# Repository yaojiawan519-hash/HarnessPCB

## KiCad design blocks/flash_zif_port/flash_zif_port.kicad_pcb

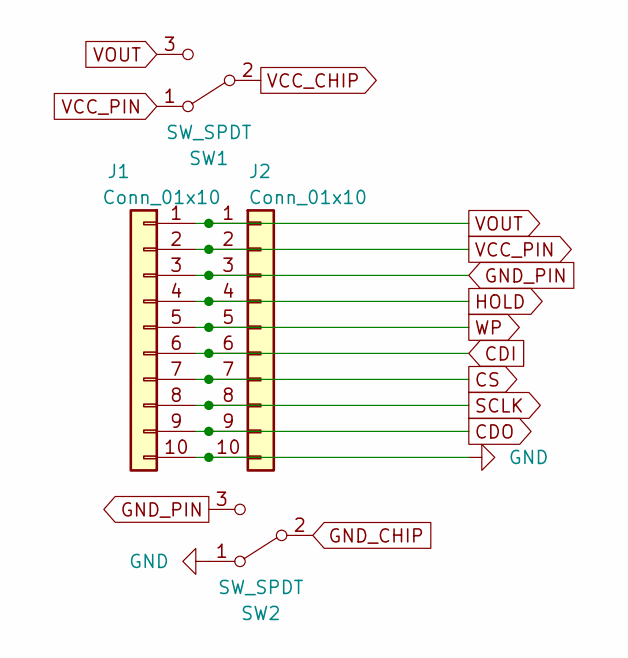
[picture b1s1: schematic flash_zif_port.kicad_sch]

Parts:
J1: Conn_01x10; PinSocket_1x10_P2.54mm_Horizontal
J2: Conn_01x10; PinHeader_1x10_P2.54mm_Vertical
SW1, SW2: SW_SPDT; SW_SPDT_PCM12

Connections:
CDI: J1.6, J2.6
CDO: J1.9, J2.9
CS: J1.7, J2.7
GND: J1.10, J2.10, SW2.1 (A)
GND_CHIP: SW2.2 (B)
GND_PIN: J1.3, J2.3, SW2.3 (C)
HOLD: J1.4, J2.4
SCLK: J1.8, J2.8
VCC_CHIP: SW1.2 (B)
VCC_PIN: J1.2, J2.2, SW1.1 (A)
VOUT: J1.1, J2.1, SW1.3 (C)
WP: J1.5, J2.5

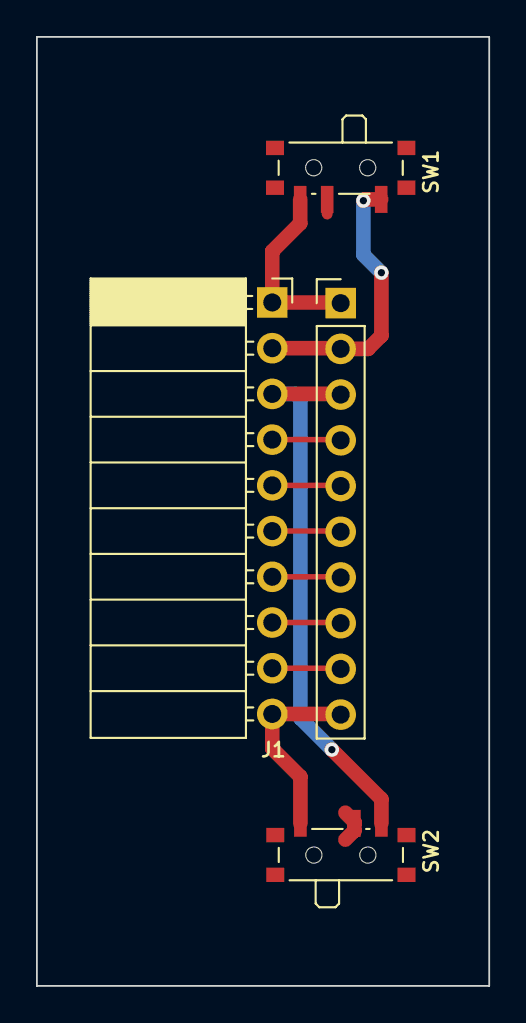
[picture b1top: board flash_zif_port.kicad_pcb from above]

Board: 2 copper layers, 25.1 x 52.7 mm, 4 parts (0 on the bottom side), 10 nets.

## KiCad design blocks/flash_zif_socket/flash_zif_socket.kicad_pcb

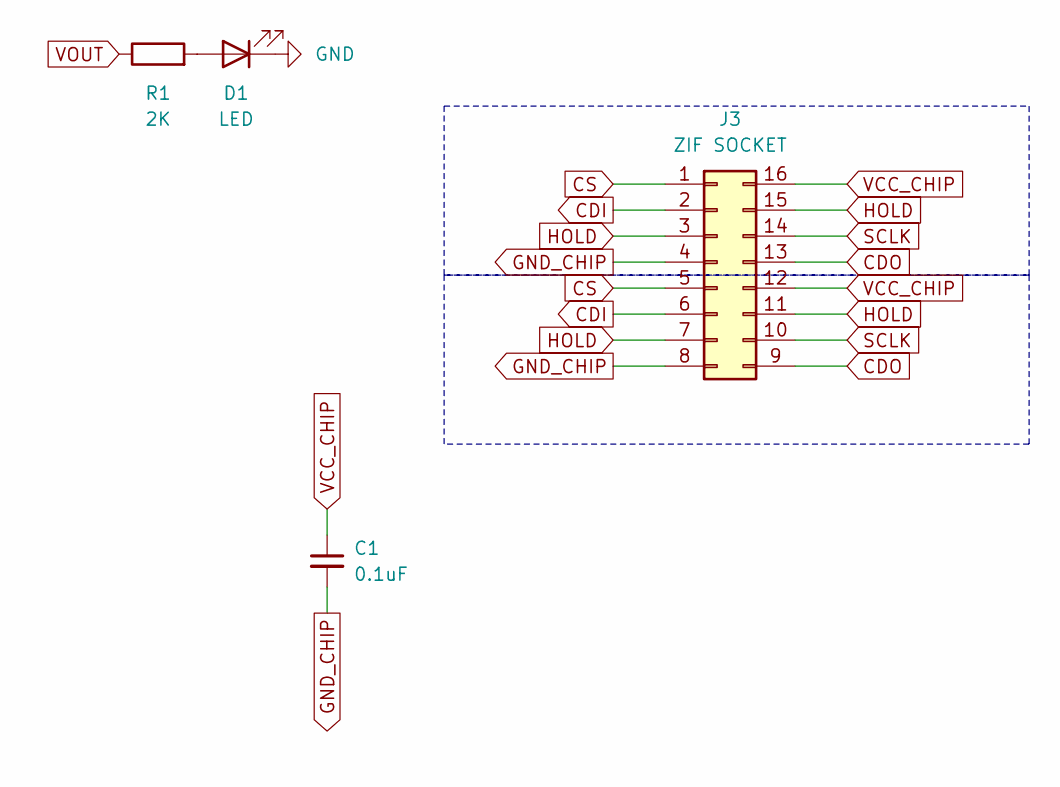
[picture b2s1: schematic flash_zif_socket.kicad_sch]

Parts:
C1: 0.1uF; C_0805_2012Metric
D1: LED; LED_0805_2012Metric
J3: ZIF SOCKET; DIP_Socket-16_W4.3_W5.08_W7.62_W10.16_W10.9_3M_216-3340-00-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
R1: 2K; R_0805_2012Metric

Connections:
CDI: J3.2, J3.6
CDO: J3.9, J3.13
CS: J3.1, J3.5
GND: D1.1 (K)
GND_CHIP: C1.2, J3.4, J3.8
HOLD: J3.3, J3.7, J3.11, J3.15
unnamed: D1.2 (A), R1.2
SCLK: J3.10, J3.14
VCC_CHIP: C1.1, J3.12, J3.16
VOUT: R1.1

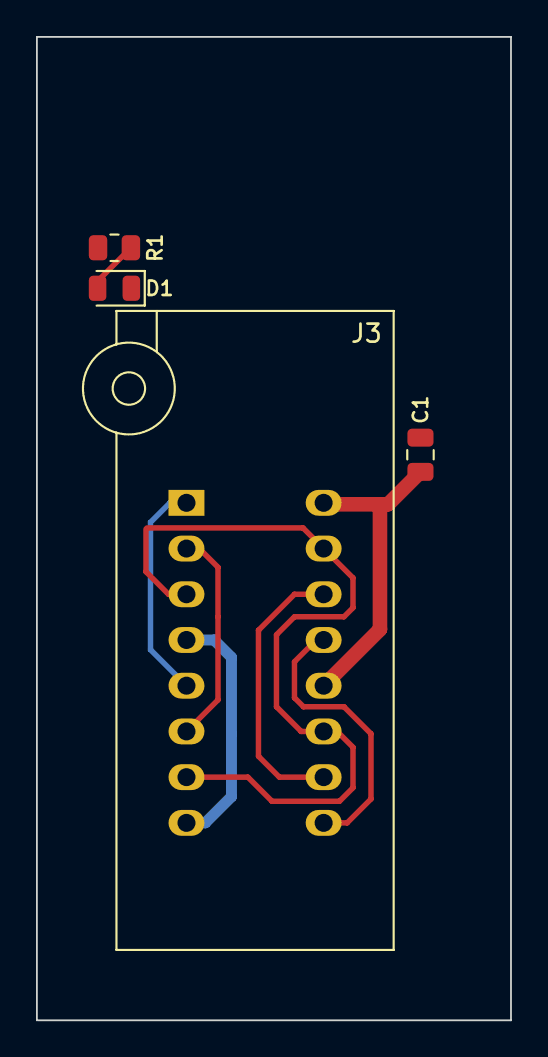
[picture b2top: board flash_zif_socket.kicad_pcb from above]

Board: 2 copper layers, 26.3 x 54.6 mm, 4 parts (0 on the bottom side), 8 nets.

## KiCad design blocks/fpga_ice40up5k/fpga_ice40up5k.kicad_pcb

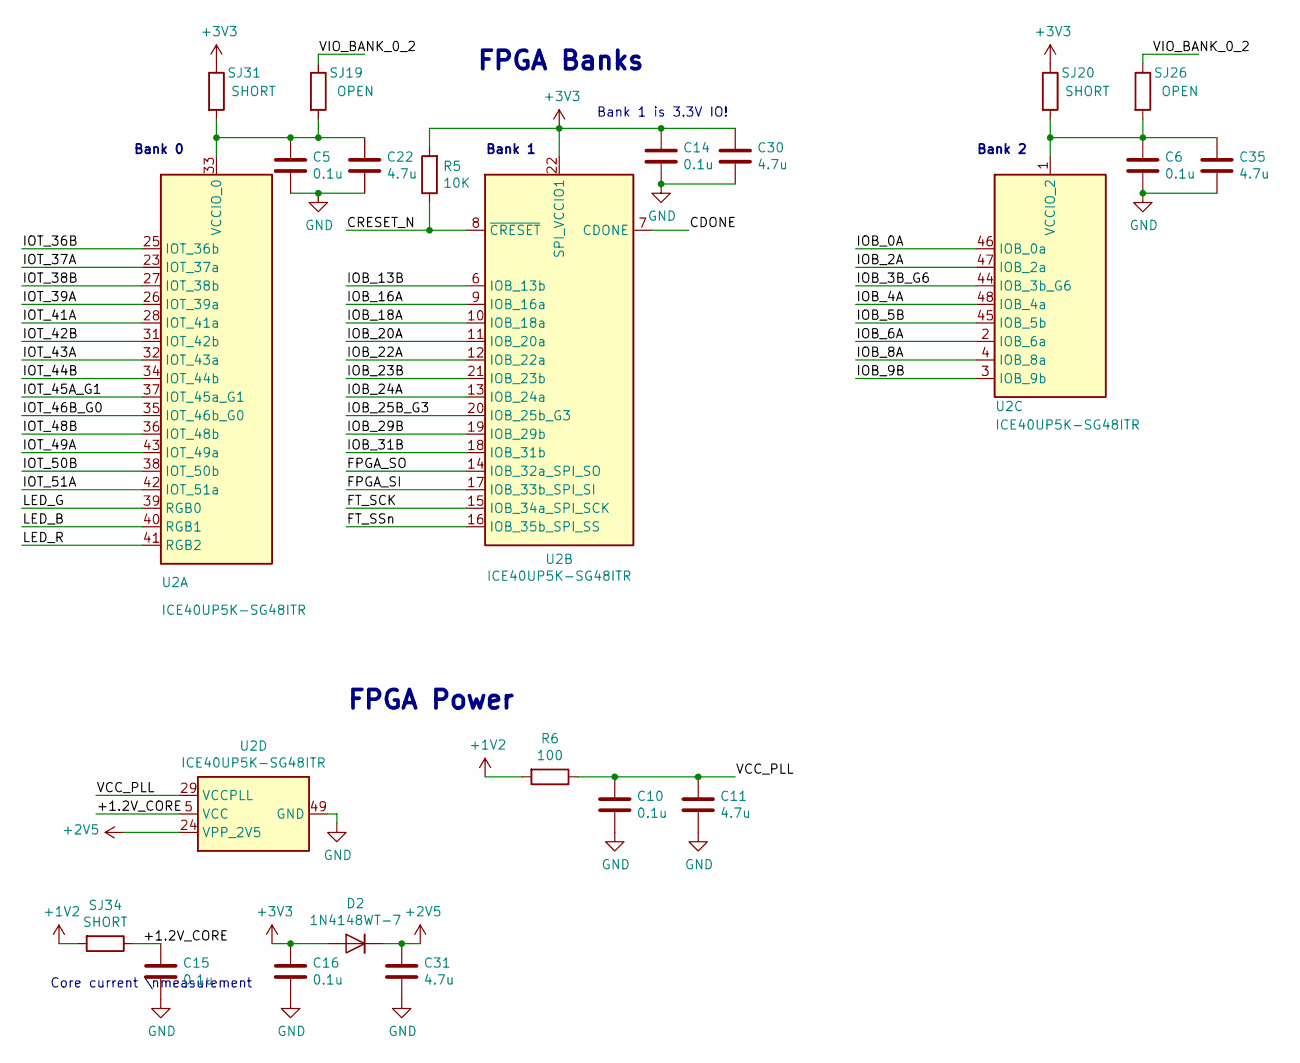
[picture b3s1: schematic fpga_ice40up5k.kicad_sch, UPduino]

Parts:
C5: 0.1u; C_0603_1608Metric; MPN C1005X5R0J104K050BA
C6, C10, C14, C15, C16: 0.1u; C_0603_1608Metric
C11, C22, C30, C31, C35: 4.7u; C_0603_1608Metric
D2: 1N4148WT-7; D_SOD-523
R5: 10K; R_0603_1608Metric
R6: 100; R_0603_1608Metric
SJ19, SJ26: OPEN; SolderJumper-2_0603_Open_TrianglePad1.0x1.5mm
SJ20, SJ31, SJ34: SHORT; ShortedJumper-2_P1.3mm_Bridged_Pad1.0x1.0mm
U2: ICE40UP5K-SG48ITR; QFN-48-1EP_7x7mm_P0.5mm_EP5.6x5.6mm

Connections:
+1V2: R6.2, SJ34.2
+2V5: C31.1, D2.1 (K), U2.24 (VPP_2V5)
+3V3: C14.1, C16.1, C30.1, D2.2 (A), R5.2, SJ20.1, SJ31.1, U2.22 (SPI_VCCIO1)
/+1.2V_CORE: C15.1, SJ34.1, U2.5 (VCC), U2.30 (VCC)
/CDONE: U2.7 (CDONE)
/CRESET_N: R5.1, U2.8 (~CRESET)
/FPGA_SI: U2.17 (IOB_33b_SPI_SI)
/FPGA_SO: U2.14 (IOB_32a_SPI_SO)
/FT_SCK: U2.15 (IOB_34a_SPI_SCK)
/FT_SSn: U2.16 (IOB_35b_SPI_SS)
/IOB_0A: U2.46 (IOB_0a)
/IOB_2A: U2.47 (IOB_2a)
/IOB_3B_G6: U2.44 (IOB_3b_G6)
/IOB_4A: U2.48 (IOB_4a)
/IOB_5B: U2.45 (IOB_5b)
/IOB_6A: U2.2 (IOB_6a)
/IOB_8A: U2.4 (IOB_8a)
/IOB_9B: U2.3 (IOB_9b)
/IOB_13B: U2.6 (IOB_13b)
/IOB_16A: U2.9 (IOB_16a)
/IOB_18A: U2.10 (IOB_18a)
/IOB_20A: U2.11 (IOB_20a)
/IOB_22A: U2.12 (IOB_22a)
/IOB_23B: U2.21 (IOB_23b)
/IOB_24A: U2.13 (IOB_24a)
/IOB_25B_G3: U2.20 (IOB_25b_G3)
/IOB_29B: U2.19 (IOB_29b)
/IOB_31B: U2.18 (IOB_31b)
/IOT_36B: U2.25 (IOT_36b)
/IOT_37A: U2.23 (IOT_37a)
/IOT_38B: U2.27 (IOT_38b)
/IOT_39A: U2.26 (IOT_39a)
/IOT_41A: U2.28 (IOT_41a)
/IOT_42B: U2.31 (IOT_42b)
/IOT_43A: U2.32 (IOT_43a)
/IOT_44B: U2.34 (IOT_44b)
/IOT_45A_G1: U2.37 (IOT_45a_G1)
/IOT_46B_G0: U2.35 (IOT_46b_G0)
/IOT_48B: U2.36 (IOT_48b)
/IOT_49A: U2.43 (IOT_49a)
/IOT_50B: U2.38 (IOT_50b)
/IOT_51A: U2.42 (IOT_51a)
/LED_B: U2.40 (RGB1)
/LED_G: U2.39 (RGB0)
/LED_R: U2.41 (RGB2)
/VCC_PLL: C10.1, C11.1, R6.1, U2.29 (VCCPLL)
/VIO_BANK_0_2: SJ19.1, SJ26.1
GND: C5.2, C6.2, C10.2, C11.2, C14.2, C15.2, C16.2, C22.2, C30.2, C31.2, C35.2, U2.49 (GND)
unnamed: C5.1, C22.1, SJ19.2, SJ31.2, U2.33 (VCCIO_0)
unnamed: C6.1, C35.1, SJ20.2, SJ26.2, U2.1 (VCCIO_2)

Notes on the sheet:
FPGA Banks
FPGA Power
Bank 2
Core current \nmeasurement
Bank 1
Bank 0
Bank 1 is 3.3V IO!

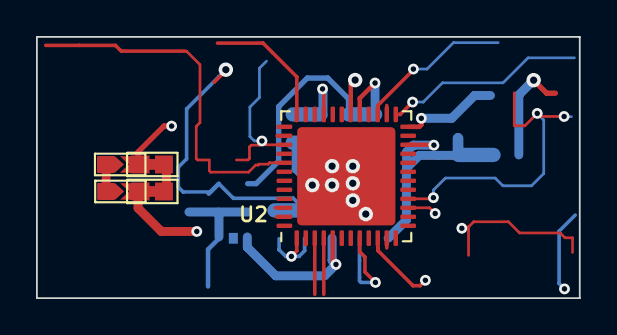
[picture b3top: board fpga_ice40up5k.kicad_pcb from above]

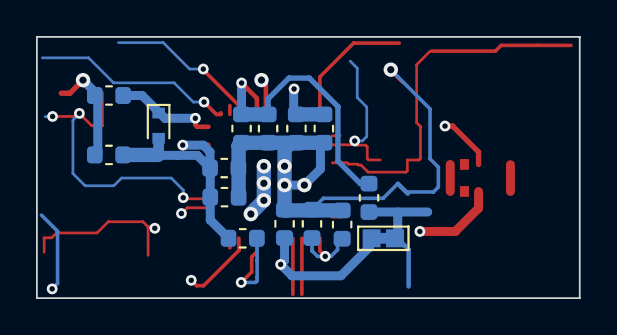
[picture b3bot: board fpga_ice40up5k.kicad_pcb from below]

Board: 4 copper layers, 30.2 x 14.5 mm, 20 parts (15 on the bottom side), 10 nets.

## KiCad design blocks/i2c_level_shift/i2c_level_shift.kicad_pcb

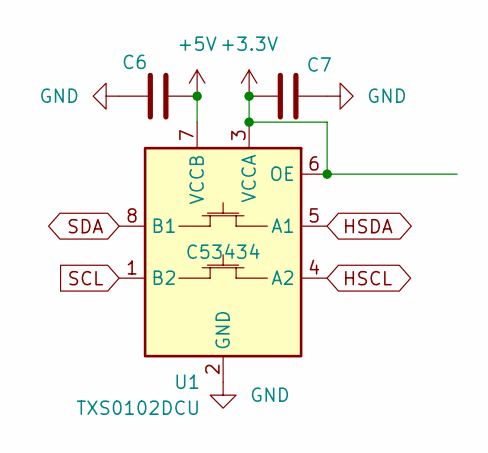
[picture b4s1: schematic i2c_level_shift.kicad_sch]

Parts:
C6, C7: 10uF/6.3V; C_0805_2012Metric
U1: TXS0102DCU; VSSOP-8_2.3x2mm_P0.5mm

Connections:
+3.3V: C7.1, U1.3 (VCCA), U1.6 (OE)
BULK_VIN: C6.2, U1.7 (VCCB)
GND: C6.1, C7.2, U1.2 (GND)
HSCL: U1.4 (A2)
HSDA: U1.5 (A1)
SCL: U1.1 (B2)
SDA: U1.8 (B1)

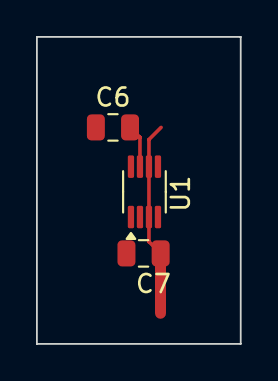
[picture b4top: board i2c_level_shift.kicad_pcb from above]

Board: 2 copper layers, 11.3 x 17.1 mm, 3 parts (0 on the bottom side), 3 nets.

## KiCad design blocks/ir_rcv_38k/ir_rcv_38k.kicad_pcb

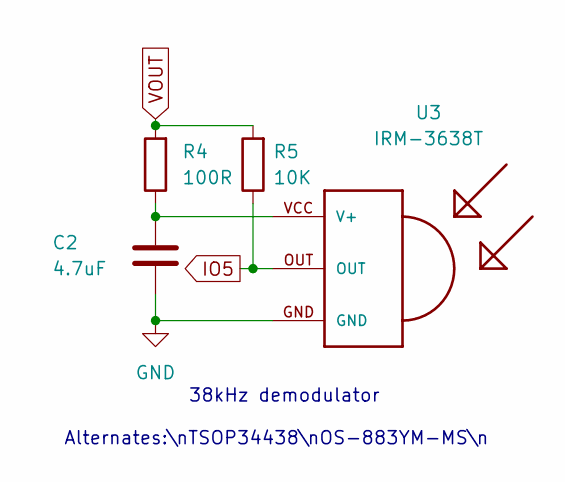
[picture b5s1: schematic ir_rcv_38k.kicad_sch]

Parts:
C2: 4.7uF; C_0805_2012Metric
R4: 100R; R_0805_2012Metric
R5: 10K; R_0805_2012Metric
U3: IRM-3638T; TSOP18XX

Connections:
GND: C2.2, U3.GND
IO5: R5.1, U3.OUT
unnamed: C2.1, R4.1, U3.VCC (V+)
VOUT: R4.2, R5.2

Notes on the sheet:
38kHz demodulator
Alternates:\nTSOP34438\nOS-883YM-MS\n

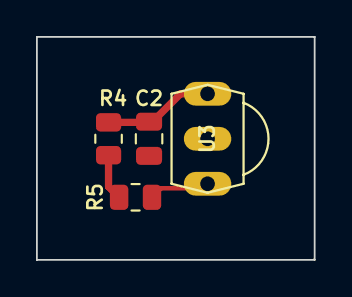
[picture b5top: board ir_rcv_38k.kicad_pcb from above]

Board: 2 copper layers, 15.4 x 12.4 mm, 4 parts (0 on the bottom side), 4 nets.

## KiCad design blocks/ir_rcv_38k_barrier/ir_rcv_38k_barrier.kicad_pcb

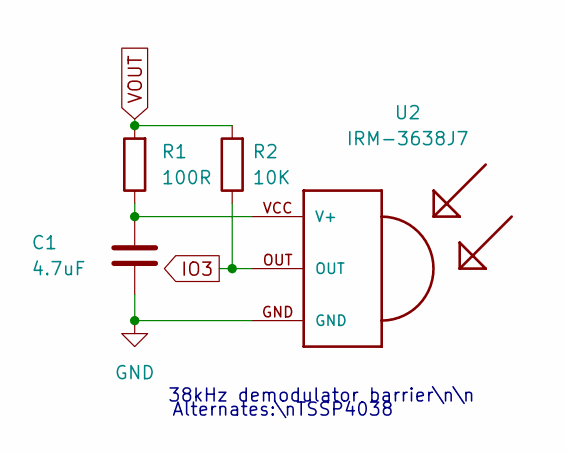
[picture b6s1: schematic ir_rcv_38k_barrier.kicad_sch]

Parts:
C1: 4.7uF; C_0805_2012Metric
R1: 100R; R_0805_2012Metric
R2: 10K; R_0805_2012Metric
U2: IRM-3638J7; TSOP18XX

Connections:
GND: C1.2, U2.GND
IO3: R2.1, U2.OUT
unnamed: C1.1, R1.1, U2.VCC (V+)
VOUT: R1.2, R2.2

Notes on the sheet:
38kHz demodulator barrier\n\n
Alternates:\nTSSP4038

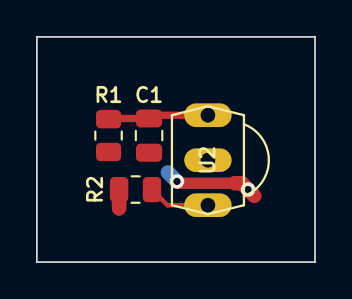
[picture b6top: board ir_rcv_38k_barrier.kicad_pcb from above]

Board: 2 copper layers, 15.5 x 12.5 mm, 4 parts (0 on the bottom side), 4 nets.

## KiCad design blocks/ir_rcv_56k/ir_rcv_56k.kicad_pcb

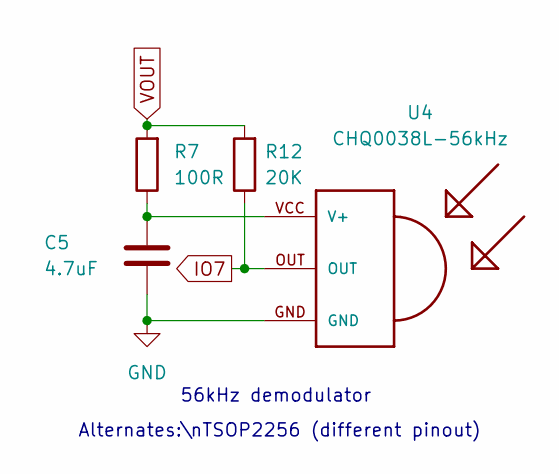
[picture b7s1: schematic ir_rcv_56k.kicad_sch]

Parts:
C5: 4.7uF; C_0805_2012Metric
R7: 100R; R_0805_2012Metric
R12: 20K; R_0805_2012Metric
U4: CHQ0038L-56kHz; TSOP18XX

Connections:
GND: C5.2, U4.GND
IO7: R12.1, U4.OUT
unnamed: C5.1, R7.1, U4.VCC (V+)
VOUT: R7.2, R12.2

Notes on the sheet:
56kHz demodulator
Alternates:\nTSOP2256 (different pinout)

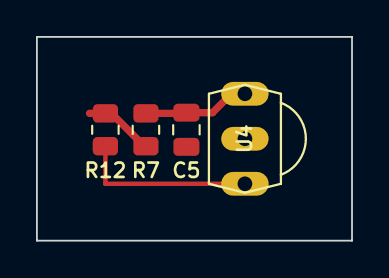
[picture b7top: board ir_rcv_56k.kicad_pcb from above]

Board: 2 copper layers, 17.5 x 11.3 mm, 4 parts (0 on the bottom side), 4 nets.

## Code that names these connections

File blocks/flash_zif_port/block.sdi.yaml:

project:
  kind: block
  name: flash_zif_port
  version: sdi/1
defs:
  flash_zif_port:
    category: connector
    rationale: '**适配板左侧那一条"输入侧"**：J1 是 1×10 卧式母座（`PinSocket_1x10_P2.54mm_Horizontal`， 本体探出板左沿，套在 Bus Pirate
      5 的排针上），J2 是同位的 1×10 竖排针 （`PinHeader_1x10_P2.54mm_Vertical`），两只**逐脚并联**，实际只焊一只。 十脚：**1=VOUT、2=VCC_PIN、3=GND_PIN、4=HOLD、5=WP、6=CDI、7=CS、8=SCLK、
      9=CDO、10=GND**——就是 SPI 闪存那六根（CS/SCLK/CDI/CDO/HOLD/WP）+ 电源地。 另加两只 SPDT 拨动开关决定芯片吃哪路电： SW1（VCC）**1=VCC_PIN、2=VCC_CHIP、3=VOUT**；SW2（GND）
      **1=GND、2=GND_CHIP、3=GND_PIN**。 十脚里其实是**两对独立电源**：1 号与 10 号是 `VOUT`/`GND`（板自己的电源）， 2 号与 3 号是 `VCC_PIN`/`GND_PIN`（主机另给的一对）——两对在**本块里并不相连**，
      只在切换开关处二选一。 ⚠ SW1 与 SW2 **必须拨到同一对**：一个给 VOUT、另一个给 GND_PIN，就把两路电源 交叉并在芯片上了。 ⚠ 本块的 `WP` 只到 J1/J2 的第
      5 脚，**ZIF 座上没有 WP 触点**（座上的第 3/7/11/15 四个触点接的是 `HOLD`）。'
    ports:
    - name: CDI
      kind: signal
      class: digital
      direction: bidirectional
      exit:
        pin: J1-6
        connector: true
      pin: J1/6
      note: 第 6 脚 → 芯片 **MISO**（`CDI` 是主控侧叫法）；J1.6 与 J2.6 同网
    - name: CDO
      kind: signal
      class: digital
      direction: bidirectional
      exit:
        pin: J1-9
        connector: true
      pin: J1/9
      note: 第 9 脚 → 芯片 **MOSI**（Controller Data Out）；J1.9 / J2.9 同网
    - name: CS
      kind: signal
      class: digital
      direction: bidirectional
      exit:
        pin: J1-7
        connector: true
      pin: J1/7
      note: 第 7 脚（片选，低有效）
    - name: GND_CHIP
      kind: signal
      class: digital
      direction: bidirectional
      exit:
        pin: SW2-2
        connector: false
      pin: SW2/2
      note: ⚠ 出口脚是 **SW2 的中间脚**：芯片地从这里出去，进 SW2 前在 GND（第 10 脚）/ GND_PIN（第 3 脚）之间二选一
    - name: HOLD
      kind: signal
      class: digital
      direction: bidirectional
      exit:
        pin: J1-4
        connector: true
      pin: J1/4
      note: 第 4 脚（HOLD# / RESET#）
    - name: SCLK
      kind: signal
      class: digital
      direction: bidirectional
      exit:
        pin: J1-8
        connector: true
      pin: J1/8
      note: 第 8 脚（时钟）
    - name: VCC_CHIP
      kind: signal
      class: digital
      direction: bidirectional
      exit:
        pin: SW1-2
        connector: false
      pin: SW1/2
      note: ⚠ 出口脚是 **SW1 的中间脚**（不是排针脚）：芯片电源从这里出去，进 SW1 前在 VOUT / VCC_PIN 之间二选一
    - name: VOUT
      kind: signal
      class: digital
      direction: bidirectional
      exit:
        pin: J1-1
        connector: true
      pin: J1/1
      note: 第 1 脚：主机 VOUT 直入，也是电源灯的取电点（灯在另一个块里）；SW1.3 也在这根网上
    rails:
    - GND
    parts:
    - ref: SW1
      lib: Switch:SW_SPDT
      value: SW_SPDT
      footprint: Button_Switch_SMD:SW_SPDT_PCM12
    - ref: SW2
      lib: Switch:SW_SPDT
      value: SW_SPDT
      footprint: Button_Switch_SMD:SW_SPDT_PCM12
    - ref: J2
      lib: Connector_Generic:Conn_01x10
      value: Conn_01x10
      footprint: Connector_PinHeader_2.54mm:PinHeader_1x10_P2.54mm_Vertical
    - ref: J1
      lib: Connector_Generic:Conn_01x10
      value: Conn_01x10
      footprint: Connector_PinSocket_2.54mm:PinSocket_1x10_P2.54mm_Horizontal
    conns:
    - ref: J1
      pin: '6'
      net: CDI
    - ref: J2
      pin: '6'
      net: CDI
    - ref: J1
      pin: '9'
      net: CDO
    - ref: J2
      pin: '9'
      net: CDO
    - ref: J1
      pin: '7'
      net: CS
    - ref: J2
      pin: '7'
      net: CS
    - ref: J1
      pin: '10'
      net: GND
    - ref: J2
      pin: '10'
      net: GND
    - ref: SW2
      pin: '1'
      net: GND
    - ref: SW2
      pin: '2'
      net: GND_CHIP
    - ref: J1
      pin: '3'
      net: GND_PIN
    - ref: J2
      pin: '3'
      net: GND_PIN
    - ref: SW2
      pin: '3'
      net: GND_PIN
    - ref: J1
      pin: '4'
      net: HOLD
    - ref: J2
      pin: '4'
      net: HOLD
    - ref: J1
      pin: '8'
      net: SCLK
    - ref: J2
      pin: '8'
      net: SCLK
    - ref: SW1
      pin: '2'
      net: VCC_CHIP
    - ref: J1
      pin: '2'
      net: VCC_PIN
    - ref: J2
      pin: '2'
      net: VCC_PIN
    - ref: SW1
      pin: '1'
      net: VCC_PIN
    - ref: J1
      pin: '1'
      net: VOUT
    - ref: J2
      pin: '1'
      net: VOUT
    - ref: SW1
      pin: '3'
      net: VOUT
    - ref: J1
      pin: '5'
      net: WP
    - ref: J2
      pin: '5'
      net: WP
    placement_prior:
      anchor: J1
      max_mm: 6.0
      rationale: 左侧竖条 18.82×44.37mm：母座贴左沿（本体本来就探出板边），竖针在其右侧 3.80mm， 两只开关一上一下夹住排针（SW1 在上 y≈68、SW2 在下 y≈106）。
        复用要点：① J2/J1 开口朝板外——这块板要**骑在**主机排针上； ② 两只开关得留在手指够得着的位置；③ 排针到 ZIF 座之间的走线在本块里就一段，别指望后面再加器件。
    slots: []
    hot_loop: []
    internal_nets:
    - GND_PIN
    - VCC_PIN
    - WP
    provenance:
      source: human:open-source
      board: Bus Pirate 5 flash adapter (DIP/ZIF) REV3
      license: MIT — 上游 Copyright (c) 2023 Ian Lesnet / Where Labs LLC
      license_tier: permissive
      author: Dangerous Prototypes（上游）/ HarnessPCB（裁块）
      date: '2026-10-30'
      kicad: 10.0.5
      basis: 4 件 / 12 网 / 端口 8 + 轨 1；铜 45 段 + 3 孔；死铜删 10；口岸切口 8；卡↔板门 ①~⑤ 全过
    geometry_status: 'extracted 2026-10-30 kicad 10.0.5（PCB 从 flash-zif-rev3.kicad_pcb 原样扣，坐标 = 源板坐标平移，origin:
      page；源板那张双面 **GND_CHIP** 灌铜（芯片侧地，不是板上 GND）是整板口岸网，按「块内不带铺铜」整张删，拼板时由整板铺铜接上）'
    notes:
    - '**适配板左侧"输入侧"**：J1 是 1×10 卧式母座（`PinSocket_1x10_P2.54mm_Horizontal`，本体探出板左沿 9.09mm、套在 Bus Pirate
      5 的排针上），J2 是同位的 1×10 竖排针（`PinHeader_1x10_P2.54mm_Vertical`），两只逐脚并联、实际只焊一只。十脚：**1=VOUT、2=VCC_PIN、3=GND_PIN、4=HOLD、5=WP、6=CDI、7=CS、8=SCLK、9=CDO、10=GND**。'
    - ⚠ `CDI` / `CDO` 是**主控侧**的名字（Controller Data In / Out）：`CDI` 接芯片的 **MISO**、`CDO` 接芯片的 **MOSI**——与芯片手册上的
      MOSI/MISO 正好相反。照名字直连会把主控的输入接到芯片的输入上。
    - 两只 SPDT 开关决定**芯片吃哪路电**：SW1（VCC）**1=VCC_PIN、2=VCC_CHIP、3=VOUT**，SW2（GND）**1=GND、2=GND_CHIP、3=GND_PIN**。所以
      `VCC_CHIP` / `GND_CHIP` 这两个端口的出口脚是**开关的中间脚**（SW1.2 / SW2.2），不是排针脚——拼板时接的就是这两个脚。⚠ 两只开关**必须拨到同一对**（都选
      VOUT/GND，或都选 VCC_PIN/GND_PIN），拨混了芯片的电源与地来自两对不同的源。
    - ⚠ 十脚里其实是**两对独立电源**：1/10 号是 `VOUT`/`GND`（主机直供的一对），2/3 号是 `VCC_PIN`/`GND_PIN`（另一对）。两对在本块里不相连，只在开关处二选一。
    - ⚠ `WP`（排针第 5 脚）在**本版到不了座**：这一族 ZIF / 16 脚 / 20 脚测试座上都**没有** WP 触点，它只连到 J1.5 ↔ J2.5 两个排针脚就断了（卡里登记为块内网
      `WP`，拼装时逐实例改名、别当端口）。要控写保护，得自己从排针第 5 脚飞一根线到芯片的 WP# 那一脚——这正是本版与 lotes / wson 两版（WP 真的到焊位）最实用的一处电路差别。
    - 几何：J1 @(138.44, 75.41) rot 0、J2 @(142.24, 75.44) rot 0（x 差 3.80mm、y 差 0.03mm，两列脚一一对齐）；SW1 @(142.24,
      68.25) rot 180、SW2 @(142.24, 105.78) rot 0。块 20.1×47.72mm（J1 的封装框从 x=127.86 起，比板左沿还外 9.09mm——这块板是**骑在**主机排针上的）。复用要点：母座开口朝板外、竖针朝上；复制块时朝向一起搬。
    - ⚠ 同族对照：本块与 `flash_sop_port` **逐件同坐标**（J1/J2/SW1/SW2 的 x/y/rot 全同），两块可以互换；铜略有差别（本块 61 段 + 5 孔，那只
      60 段 + 6 孔）。四块 `*_port` 里 J1/J2 处处相同，**只有 SW1/SW2 的 y 会动**（这一族差 1.85mm），所以四块都得按板各留一份，不能共用一个块。
    - '⚠ 这一族四张板子的**灌铜是 `GND_CHIP`（芯片侧地），不是 `GND`**。所以「块内不带铺铜」删掉的是芯片地，裂岛/裸脚全落在 `GND_CHIP` 上；`GND`（排针第 10
      脚、灯的回流）本来就没有铺铜，只靠走线。卡里 `GND_CHIP` 记在 **ports** 下、`kind: signal`——那是引擎的规则（rails 只收电源符号 `#PWR`，本板作者用的是全局标签）；它电学上是**芯片的电源/地网**，拼板时按同名接，别当信号口去串阻容。'
    - 铜 45 段 + 3 孔（B 8 / F 53）；死铜删 10 段/孔（两端全悬空、谁也连不上的才算）；口岸切口 8 处（一端悬空=块的铜接口，按用户拍板留着）、走线出口 8 处；削剩残迹留
      5 段（残迹长度只是窗口参数的函数、不是人的设计）；铺铜带走 0 张（源板那张双面 GND_CHIP 灌铜是整板口岸网，按「块内不带铺铜」整张删，拼板时重铺）。
    - 块里每个脚都有铜可接（没有"只靠铺铜连"的焊盘）。
    - kicad-cli DRC：isolated_copper 0；未连通 **0** 条；断头走线 8 + 悬空过孔 2 处就是"口岸切口"（铜走到窗口边就停 = 块的铜接口，留着）；lib_footprint_*
      2 条（源板自带，见基线）；源板 flash-zif-rev3.kicad_pcb 基线：未连通 0 / isolated_copper 0 / 违规 67 条。
